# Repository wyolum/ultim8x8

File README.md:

# ultim8x8

ultim8x8 is an APA102 RGB LED based panel consisting of 8x8 matrix. Panels can be chained to produce larger matrices. Besides +5V and GND, each board requires a CLocK and DATa signal. Each board has CLocK and DATa IN and OUT terminals. When cascading boards, the OUT from one board goes to the IN of the next board.

Each LED can require up to 60mA current at 5V for White light at full brightness. This means driving ALL the 64 LEDs at full brightness White color will require 3.8A Amps. You can get away with lower Amps if you drive LEDs at lower brightness or don't light them all up at the same time.

Boards can be cascaded using several methods. Simplest, which requires no soldering, is to screw in the supplied metal posts to the terminals marked +5V, GND, DI__A, CI__A, DO__H and CO__H. The Boards can then be interconnected using the ultim_BUS busbar, or copper tape stuck over a piece of acrylic.

When running at low Amps or driving a single board, the 4 pin 0.1" pitch header can be used.

## kicad

* [ultim8x8_v0](/kicad/ultim_8x8_v0) - first version, Main hardware design files. Schematic, Layout etc. (deprecated)
* [ultim8x8_v1](/kicad/ultim_8x8_v1) - second version, Main hardware design files. Schematic, Layout etc. (deprecated)
* [ultim8x8_v2](/kicad/ultim_8x8_v2) - third version, Main hardware design files. Schematic, Layout etc. (current)

* [ultim_bus_v1](/kicad/ultim_bus_v1) - first version, Hardware design files for a bus bar to inter-connect ultim8x8's (deprecated)
* [ultim_bus_v2](/kicad/ultim_bus_v2) - second version, Hardware design files for a bus bar to inter-connect ultim8x8's (deprecated)
* [ultim_bus_v3](/kicad/ultim_bus_v3) - third version, Hardware design files for a bus bar to inter-connect ultim8x8's (deprecated)
* [ultim_bus_v4](/kicad/ultim_bus_v4) - fourth version, Hardware design files for a bus bar to inter-connect ultim8x8's (deprecated)
* [ultim_bus_v5](/kicad/ultim_bus_v5) - fifth version, Hardware design files for a bus bar to inter-connect ultim8x8's (current)

* [ultim_bus_conn](/kicad/ultim_bus_conn) - connector strips to join multiple ultim__bus_bars

* [featherboard](/kicad/featherboard) - first version, Interface board to connect Adafruit Feather Huzzah board to ultim8x8
* [feather_v2](/kicad/feather_v2) - second version, Interface board to connect Adafruit Feather Huzzah board to ultim8x8
* [feather_v3](/kicad/feather_v3) - third version, Interface board to connect Adafruit Feather Huzzah board to ultim8x8

* [ultim8x8_data](/kicad/ultim8x8_data) - Data sheets, logos etc

## fabricate

* [buckle](/fabricate/buckle) - 3D CAD files for a Belt Buckle.
* [featherboard_case](/fabricate/featherboard_case) - 3D CAD files for a "wireless" ultim8x8 brick

License
-------
[CERN Open Hardware Licence v1.2 ]

[CERN Open Hardware Licence v1.2 ]:http://www.ohwr.org/attachments/2388/cern_ohl_v_1_2.txt

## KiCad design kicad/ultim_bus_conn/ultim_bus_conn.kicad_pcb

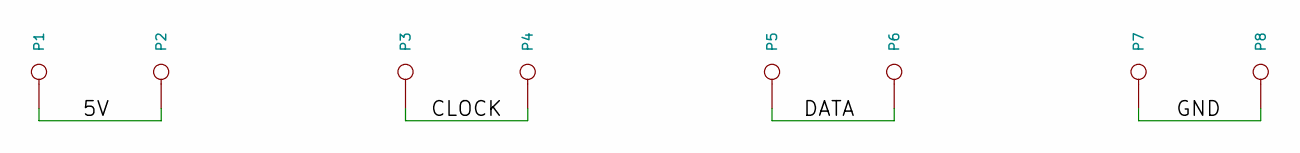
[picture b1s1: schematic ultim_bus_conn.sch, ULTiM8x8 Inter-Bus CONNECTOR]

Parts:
P1, P2, P3, P4, P5, P6, P7, P8: CONN_1; Screw

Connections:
/5V: P1.1, P2.1
/CLOCK: P3.1, P4.1
/DATA: P5.1, P6.1
/GND: P7.1, P8.1

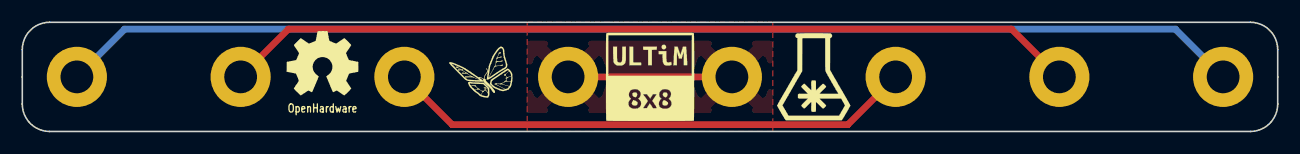
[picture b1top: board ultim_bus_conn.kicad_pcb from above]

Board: 2 copper layers, 116.8 x 10.2 mm, 10 parts (1 on the bottom side), 4 nets.

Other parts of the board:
L101, L101#2: OSHW; OSHW_6mm

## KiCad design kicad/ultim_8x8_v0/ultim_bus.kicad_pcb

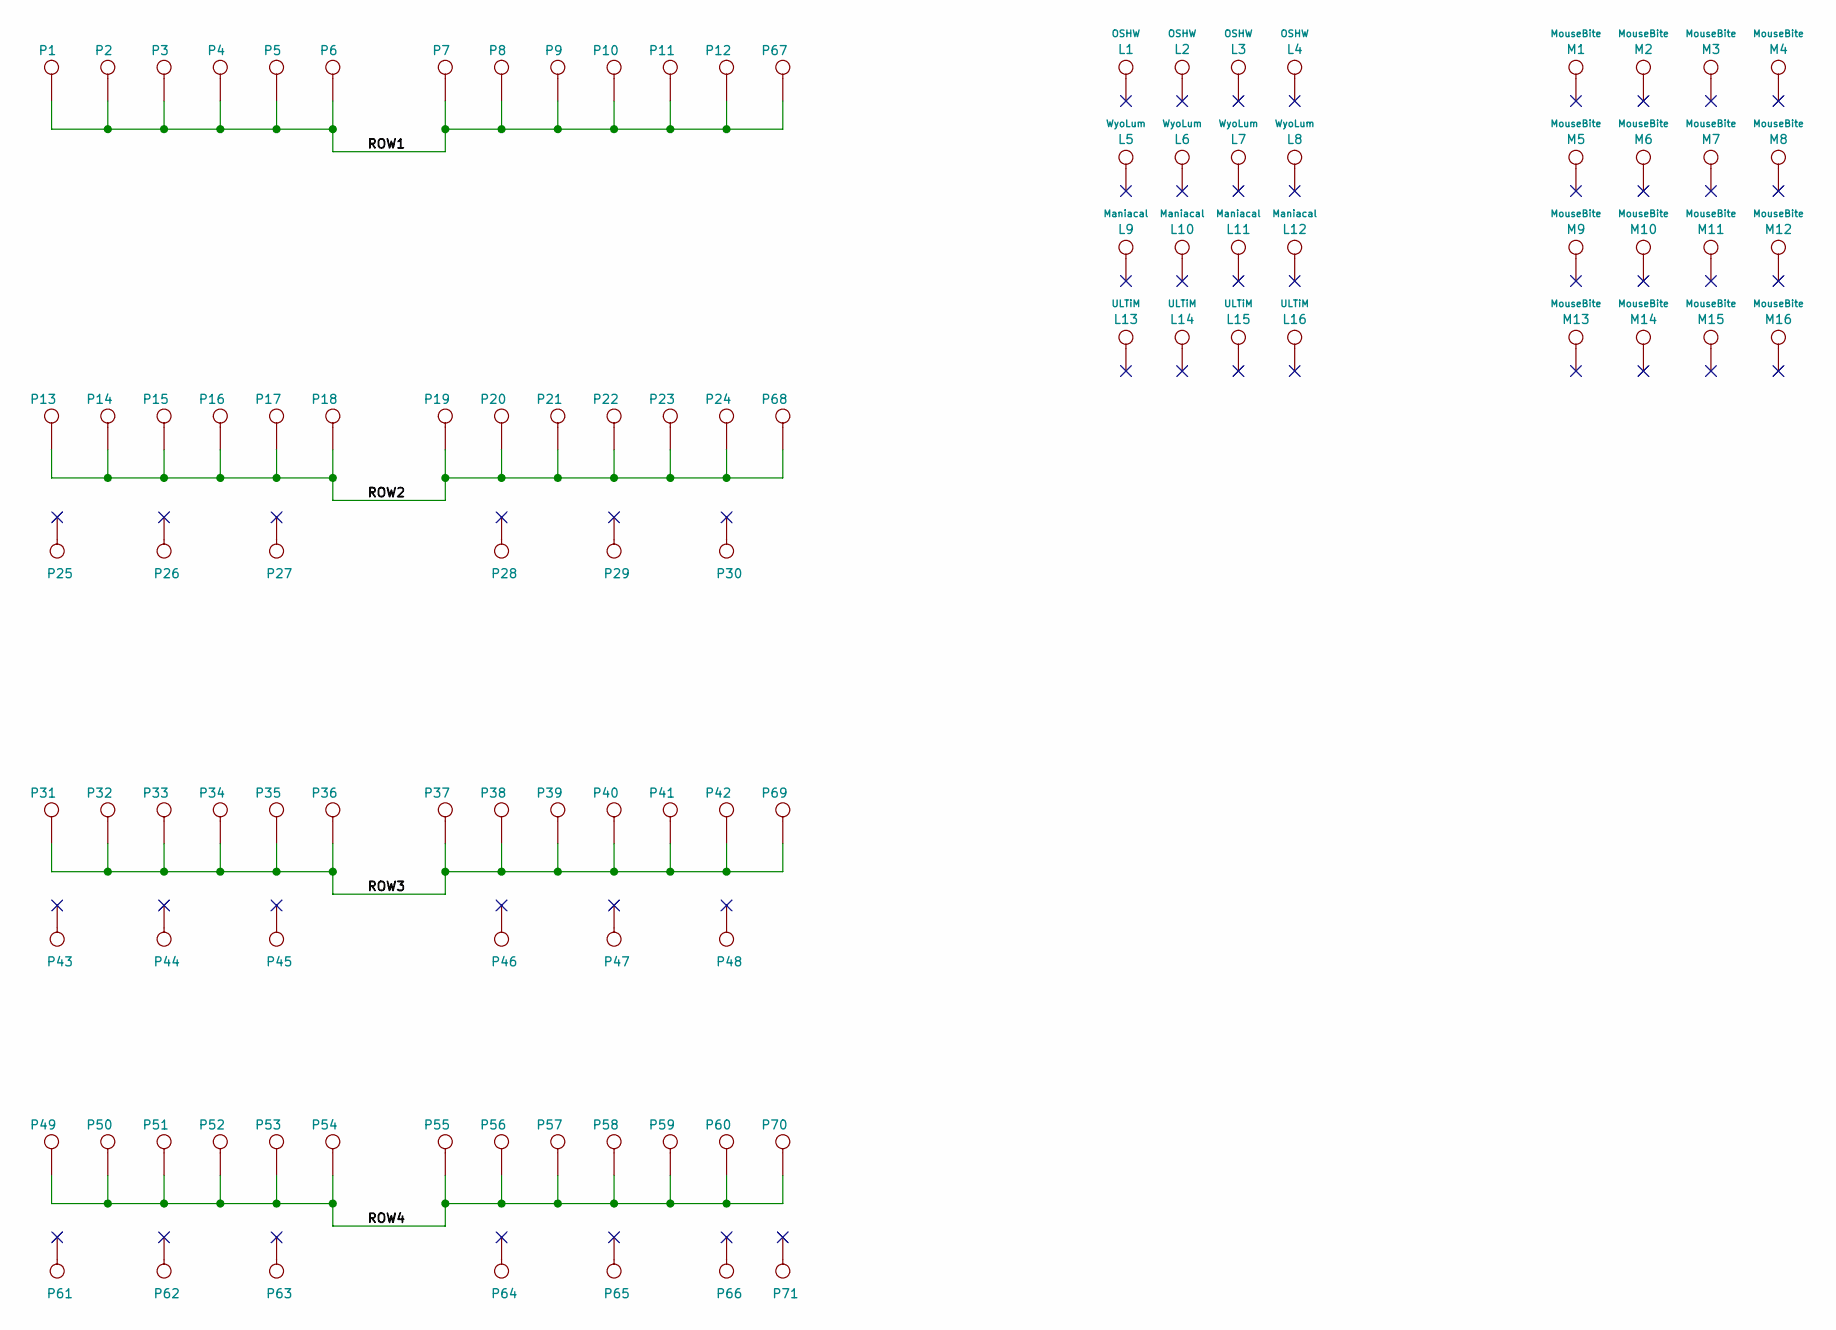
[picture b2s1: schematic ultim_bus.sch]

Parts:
L1, L2, L3, L4: OSHW; OSHW_6mm
L5, L6, L7, L8: WyoLum; logo_wyo_butterfly_small
L9, L10, L11, L12: Maniacal; logo_MLlabs_small
L13, L14, L15, L16: ULTiM; logo_ultim8x8_small
M1, M2, M3, M4, M5, M6, M7, M8, M9, M10, M11, M12, M13, M14, M15, M16: MouseBite; mouse-bite-2.54mm-slot
P1, P2, P3, P4, P5, P6, P7, P8, P9, P10, P11, P12, P13, P14, P15, P16, P17, P18, P19, P20, P21, P22, P23, P24, P25, P26, P27, P28, P29, P30, P31, P32, P33, P34, P35, P36, P37, P38, P39, P40, P41, P42, P43, P44, P45, P46, P47, P48, P49, P50, P51, P52, P53, P54, P55, P56, P57, P58, P59, P60, P61, P62, P63, P64, P65, P66, P67, P68, P69, P70, P71: CONN_1; Screw

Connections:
/ROW1: P1.1, P2.1, P3.1, P4.1, P5.1, P6.1, P7.1, P8.1, P9.1, P10.1, P11.1, P12.1, P67.1
/ROW2: P13.1, P14.1, P15.1, P16.1, P17.1, P18.1, P19.1, P20.1, P21.1, P22.1, P23.1, P24.1, P68.1
/ROW3: P31.1, P32.1, P33.1, P34.1, P35.1, P36.1, P37.1, P38.1, P39.1, P40.1, P41.1, P42.1, P69.1
/ROW4: P49.1, P50.1, P51.1, P52.1, P53.1, P54.1, P55.1, P56.1, P57.1, P58.1, P59.1, P60.1, P70.1

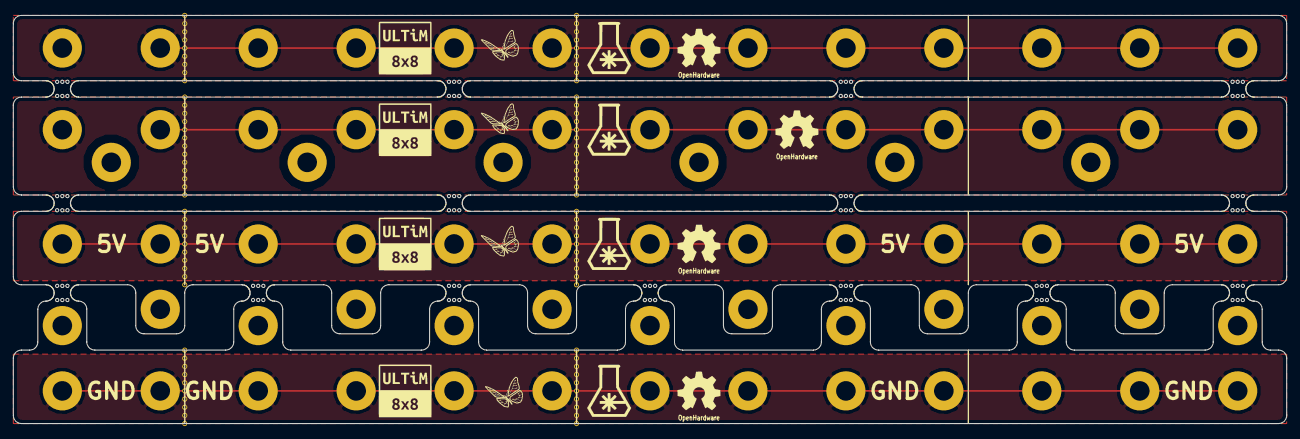
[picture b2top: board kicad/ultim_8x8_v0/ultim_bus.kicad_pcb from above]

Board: 2 copper layers, 198.1 x 63.5 mm, 102 parts (0 on the bottom side), 4 nets.

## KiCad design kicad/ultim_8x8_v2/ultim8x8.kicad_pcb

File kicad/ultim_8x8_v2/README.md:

# ultim_8x8

ultim8x8 is an APA102 RGB LED based panel consisting of 8x8 matrix. Panels can be chained to produce larger matrices. Besides +5V and GND, each board requires a CLocK and DATa signal. Each board has CLocK and DATa IN and OUT terminals. When cascading boards, the OUT from one board goes to the IN of the next board.

Each LED can require up to 60mA current at 5V for White light at full brightness. This means driving ALL the 64 LEDs at full brightness White color will require 3.8A Amps. You can get away with lower Amps if you drive LEDs at lower brightness or don't light them all up at the same time.

Boards can be cascaded using several methods. Simplest, which requires no soldering, is to screw in the supplied metal posts to the terminals marked +5V, GND, D_IN, C_IN, D_OUT and C_OUT. The Boards can then be interconnected using the ultim_BUS busbar, or copper tape stuck over a piece of acrylic.

When running at low Amps or driving a single board, the 4 pin 0.1" pitch headers can be used. There are two pairs of headers marked In1/Out1 and In2/Out2.

License
-------
[CERN Open Hardware Licence v1.2 ]

[CERN Open Hardware Licence v1.2 ]:http://www.ohwr.org/attachments/2388/cern_ohl_v_1_2.txt

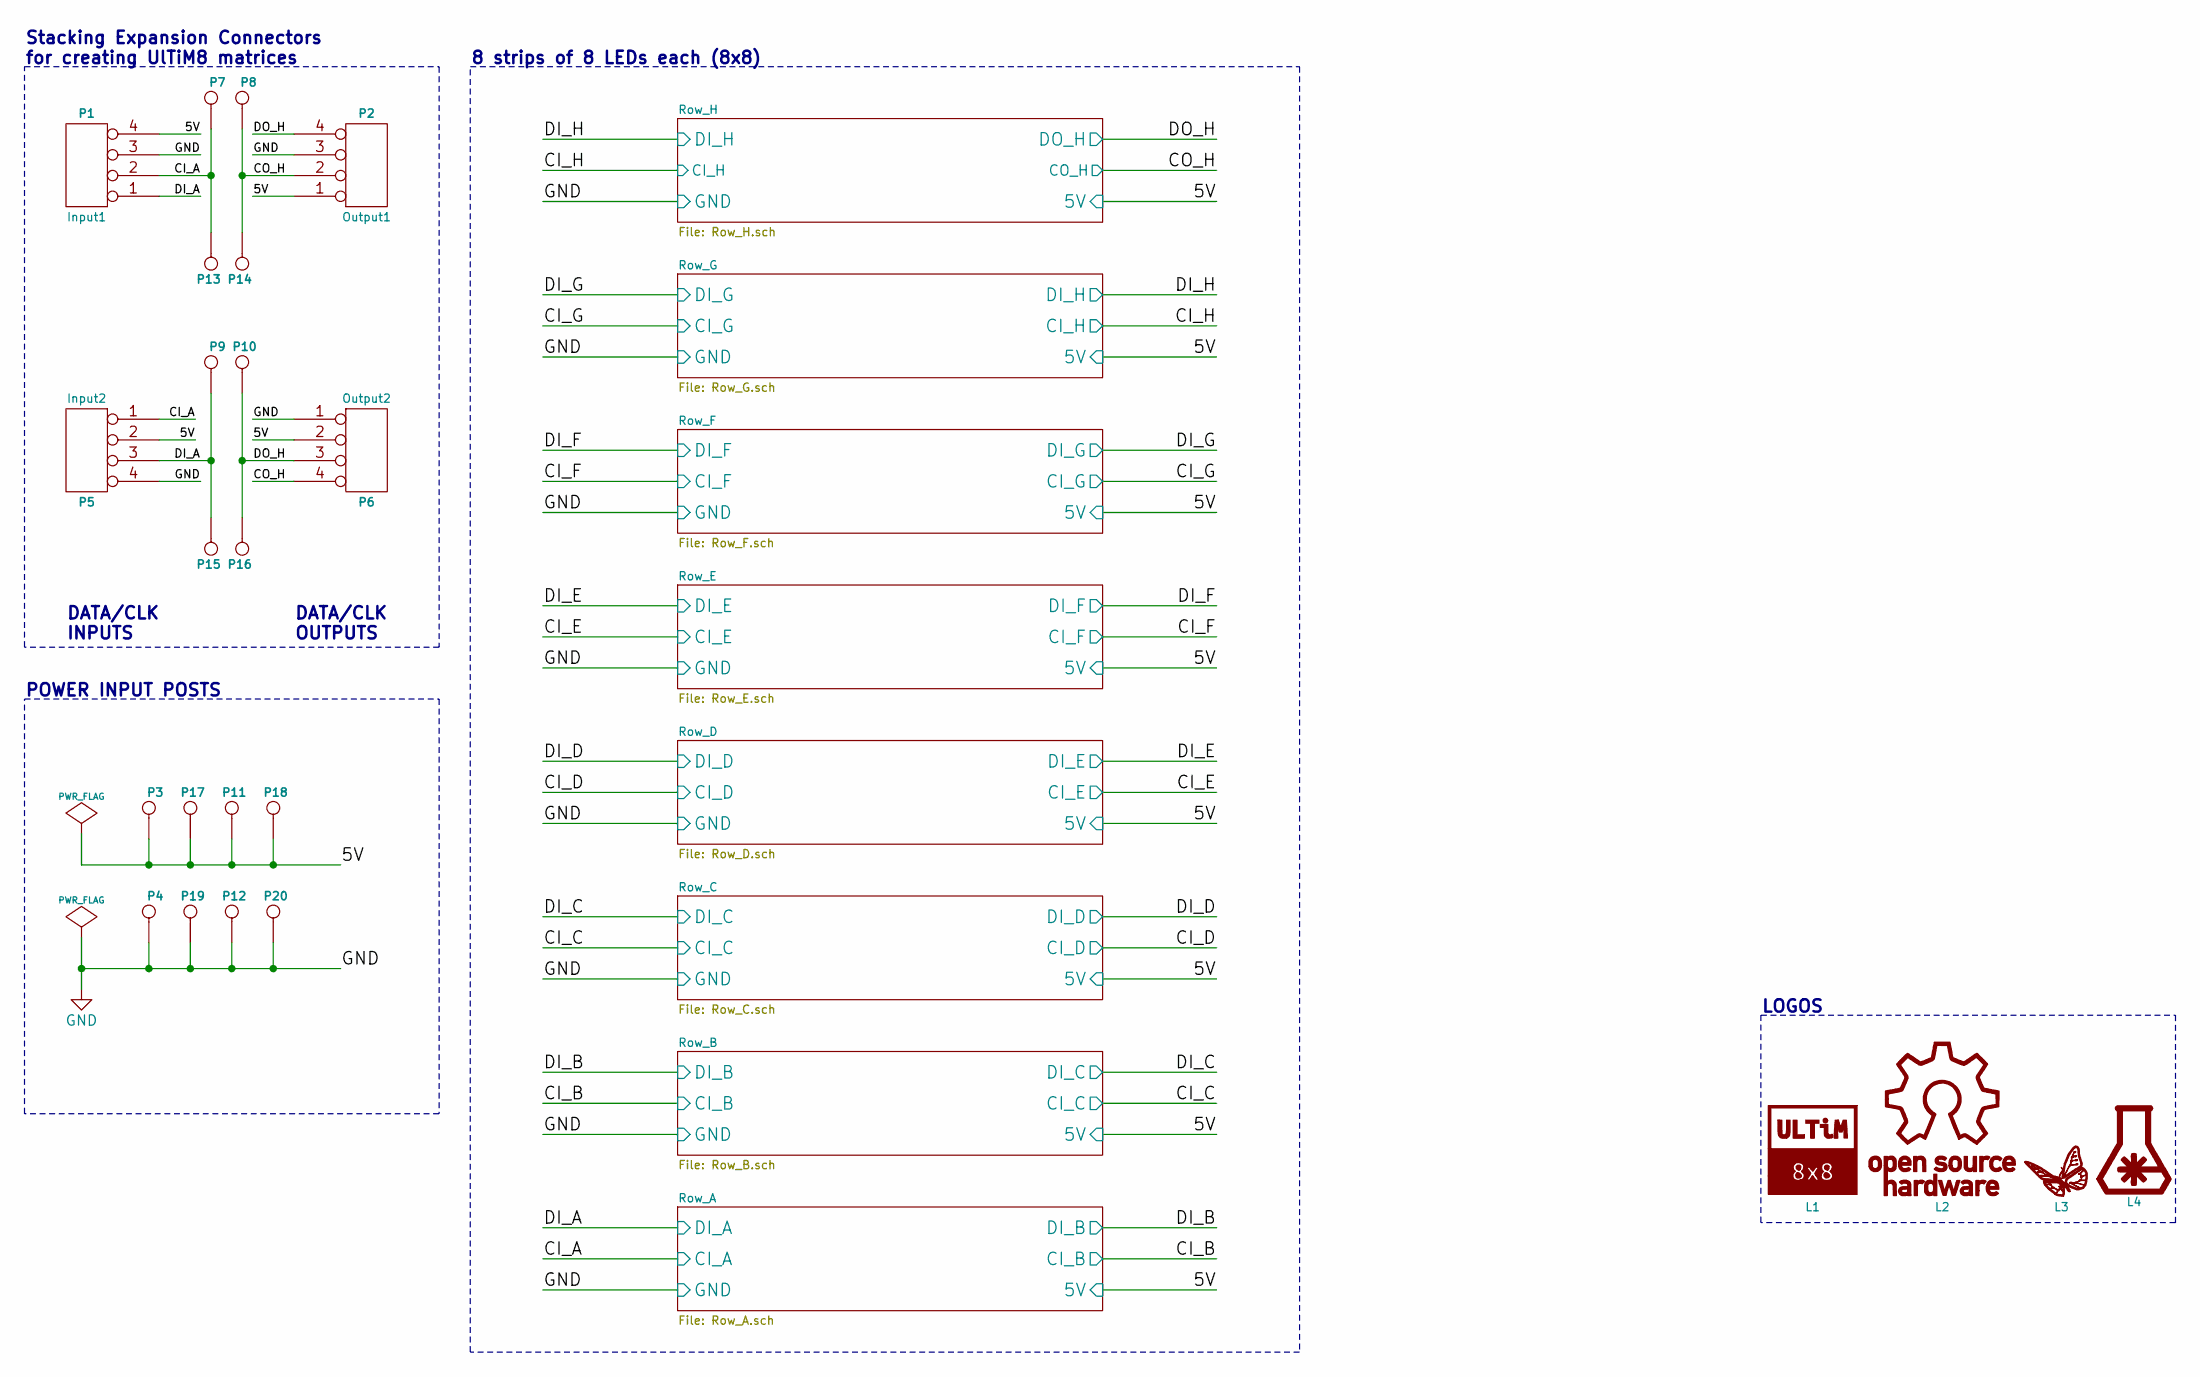
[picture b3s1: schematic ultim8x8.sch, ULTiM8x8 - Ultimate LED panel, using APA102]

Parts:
L1: ULTiM8x8; logo_ultim8x8_7mm
L2: OSHW; OSHW_6mm
L3: Wyolum; logo_wyo_butterfly_5mm
L4: Maniacal Labs; logo_MLlabs_5mm
P1: Input1; header_2x2pos_th_male
P2: Output1; header_2x2pos_th_male
P3, P11, P17, P18: 5V; Screw
P4, P12, P19, P20: GND; Screw
P5: Input2; header_2x2pos_th_male
P6: Output2; header_2x2pos_th_male
P7, P13: CI_A; Screw
P8, P14: CO_H; Screw
P9, P15: DI_A; Screw
P10, P16: DO_H; Screw

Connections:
/5V: P1.4, P2.1, P3.1, P5.2, P6.2, P11.1, P17.1, P18.1; also elsewhere on the board
/CI_A: P1.2, P5.1, P7.1, P13.1; also elsewhere on the board
/CO_H: P2.2, P6.4, P8.1, P14.1; also elsewhere on the board
/DI_A: P1.1, P5.3, P9.1, P15.1; also elsewhere on the board
/DO_H: P2.4, P6.3, P10.1, P16.1; also elsewhere on the board
GND: P1.3, P2.3, P4.1, P5.4, P6.1, P12.1, P19.1, P20.1; also elsewhere on the board

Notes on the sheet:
Stacking Expansion Connectors for creating UlTiM8 matrices
LOGOS
POWER INPUT POSTS
DATA/CLK OUTPUTS
DATA/CLK INPUTS
8 strips of 8 LEDs each (8x8)

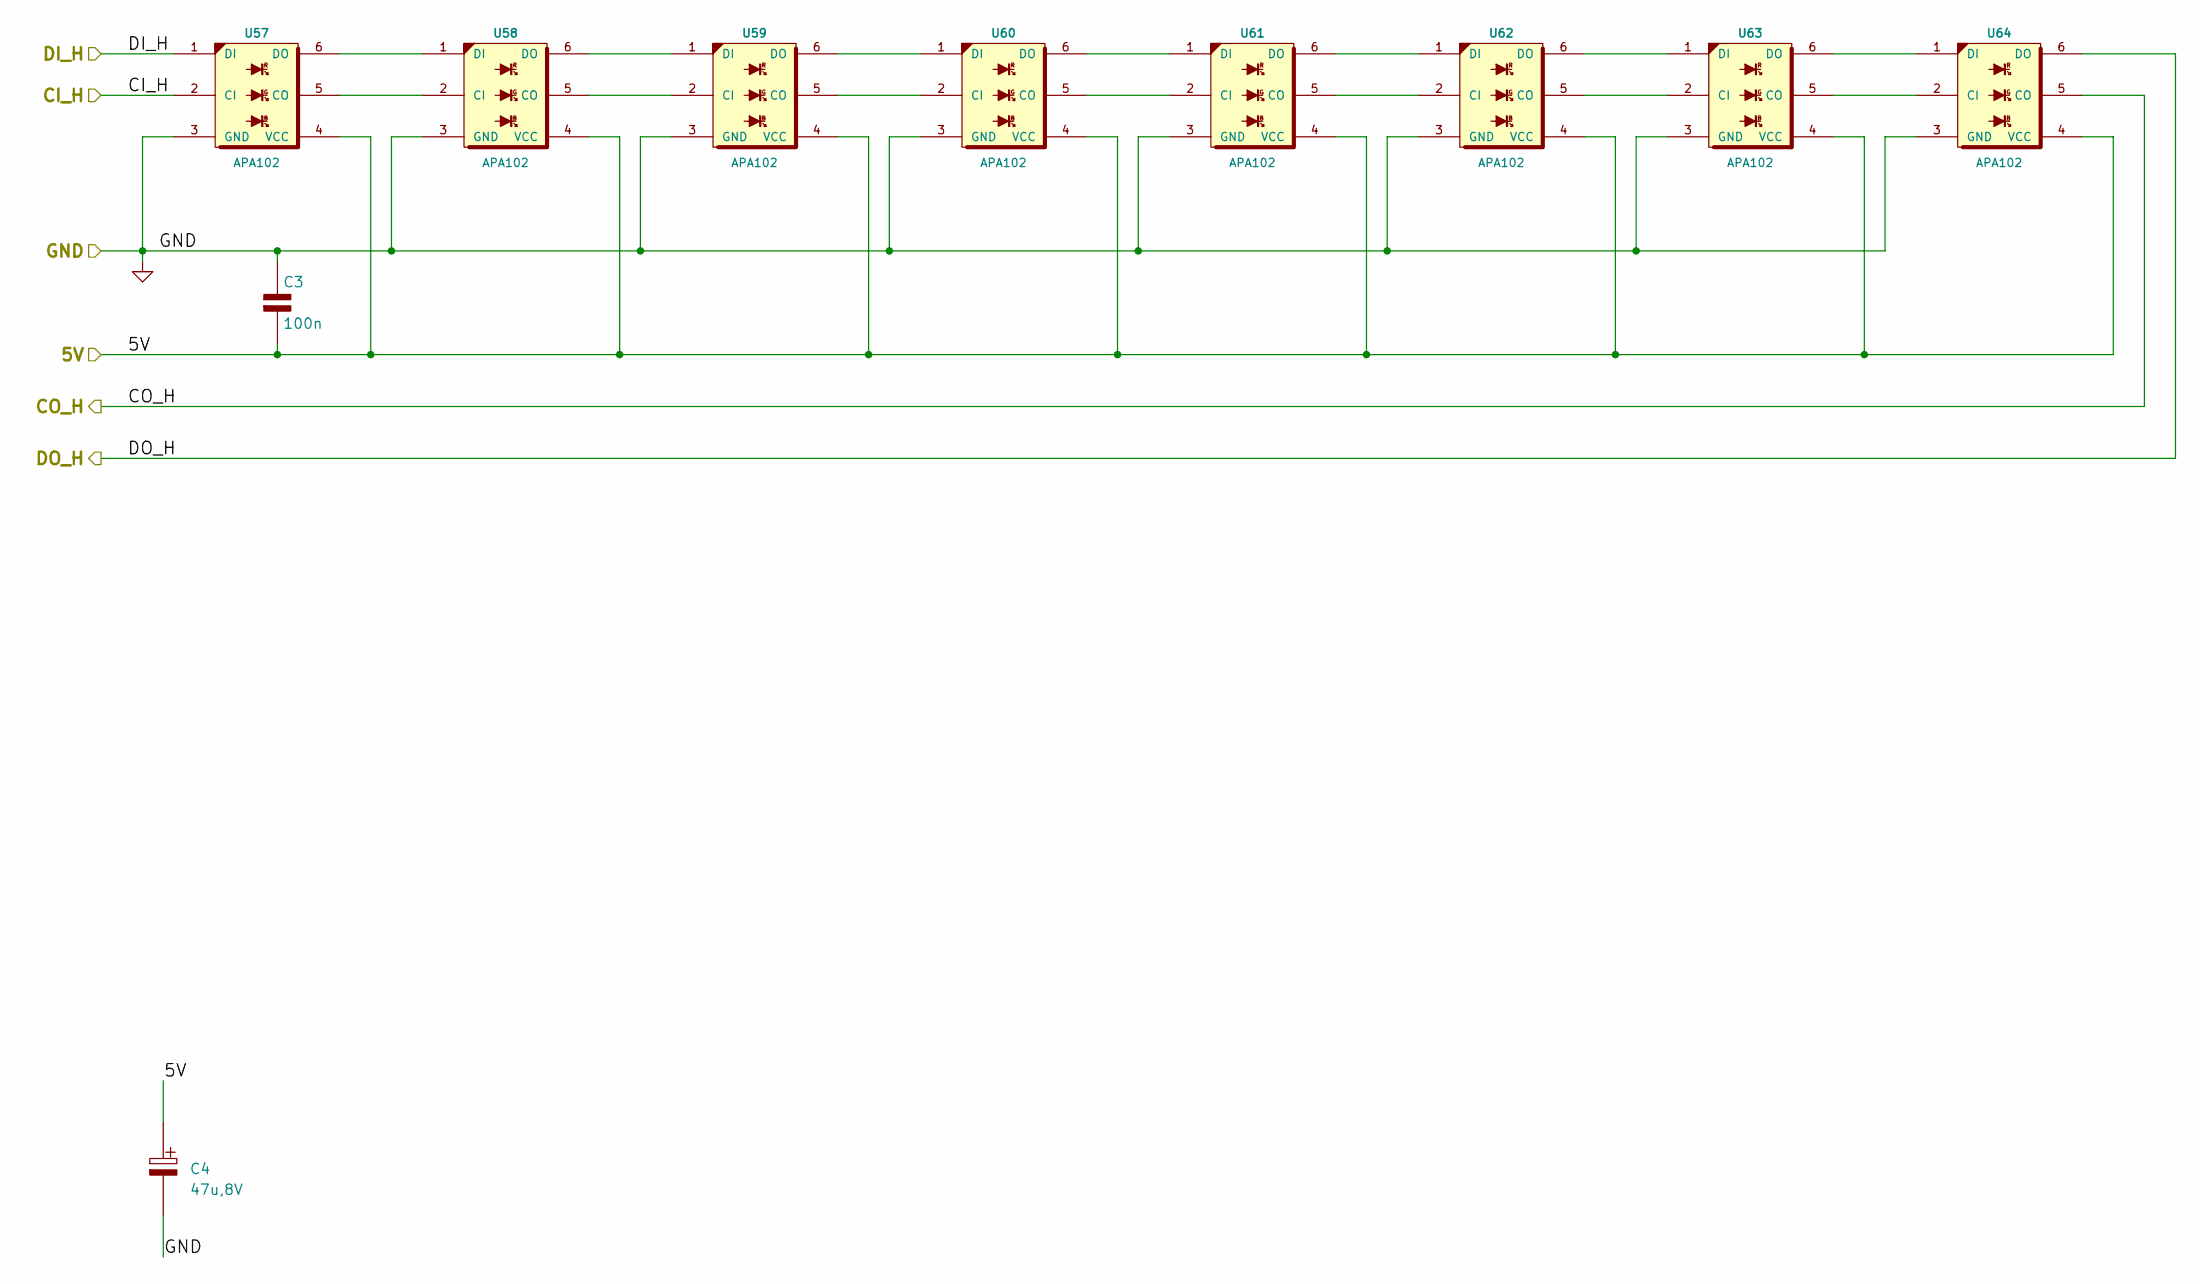
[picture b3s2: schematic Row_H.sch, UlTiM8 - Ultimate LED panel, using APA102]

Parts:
C3: 100n; c_0805
C4: 47u,8V; c_2917
U57, U58, U59, U60, U61, U62, U63, U64: APA102

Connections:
/5V: C3.2, C4.1 (+), U57.4 (VCC), U58.4 (VCC), U59.4 (VCC), U60.4 (VCC), U61.4 (VCC), U62.4 (VCC), U63.4 (VCC), U64.4 (VCC); also elsewhere on the board
/CI_H: U57.2 (CI); also elsewhere on the board
/CO_H: U64.5 (CO); also elsewhere on the board
/DI_H: U57.1 (DI); also elsewhere on the board
/DO_H: U64.6 (DO); also elsewhere on the board
GND: C3.1, C4.2 (-), U57.3 (GND), U58.3 (GND), U59.3 (GND), U60.3 (GND), U61.3 (GND), U62.3 (GND), U63.3 (GND), U64.3 (GND); also elsewhere on the board
unnamed: U57.5 (CO), U58.2 (CI)
unnamed: U57.6 (DO), U58.1 (DI)
unnamed: U58.5 (CO), U59.2 (CI)
unnamed: U58.6 (DO), U59.1 (DI)
unnamed: U59.5 (CO), U60.2 (CI)
unnamed: U59.6 (DO), U60.1 (DI)
unnamed: U60.5 (CO), U61.2 (CI)
unnamed: U60.6 (DO), U61.1 (DI)
unnamed: U61.5 (CO), U62.2 (CI)
unnamed: U61.6 (DO), U62.1 (DI)
unnamed: U62.5 (CO), U63.2 (CI)
unnamed: U62.6 (DO), U63.1 (DI)
unnamed: U63.5 (CO), U64.2 (CI)
unnamed: U63.6 (DO), U64.1 (DI)

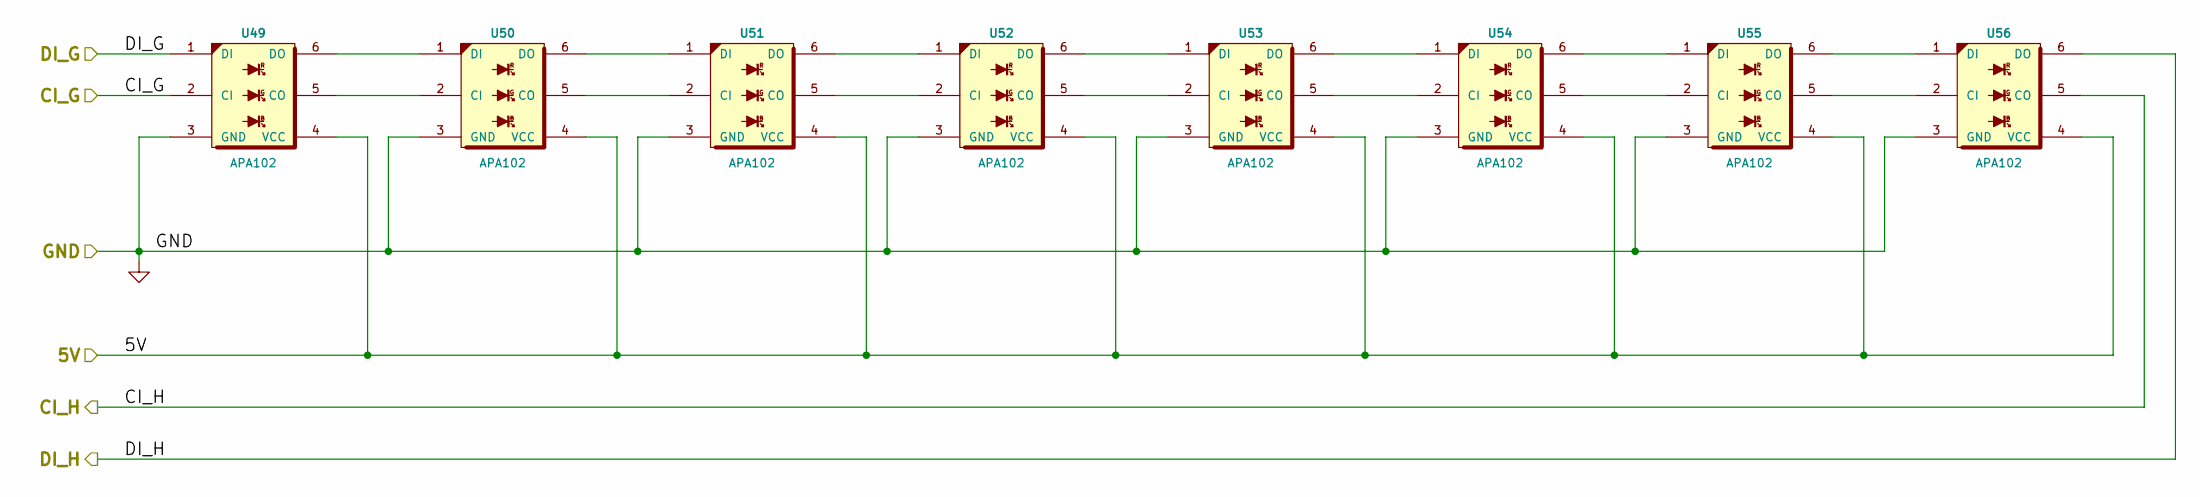
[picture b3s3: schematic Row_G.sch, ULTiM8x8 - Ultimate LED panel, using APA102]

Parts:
U49, U50, U51, U52, U53, U54, U55, U56: APA102

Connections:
/5V: U49.4 (VCC), U50.4 (VCC), U51.4 (VCC), U52.4 (VCC), U53.4 (VCC), U54.4 (VCC), U55.4 (VCC), U56.4 (VCC); also elsewhere on the board
/CI_G: U49.2 (CI); also elsewhere on the board
/CI_H: U56.5 (CO); also elsewhere on the board
/DI_G: U49.1 (DI); also elsewhere on the board
/DI_H: U56.6 (DO); also elsewhere on the board
GND: U49.3 (GND), U50.3 (GND), U51.3 (GND), U52.3 (GND), U53.3 (GND), U54.3 (GND), U55.3 (GND), U56.3 (GND); also elsewhere on the board
unnamed: U49.5 (CO), U50.2 (CI)
unnamed: U49.6 (DO), U50.1 (DI)
unnamed: U50.5 (CO), U51.2 (CI)
unnamed: U50.6 (DO), U51.1 (DI)
unnamed: U51.5 (CO), U52.2 (CI)
unnamed: U51.6 (DO), U52.1 (DI)
unnamed: U52.5 (CO), U53.2 (CI)
unnamed: U52.6 (DO), U53.1 (DI)
unnamed: U53.5 (CO), U54.2 (CI)
unnamed: U53.6 (DO), U54.1 (DI)
unnamed: U54.5 (CO), U55.2 (CI)
unnamed: U54.6 (DO), U55.1 (DI)
unnamed: U55.5 (CO), U56.2 (CI)
unnamed: U55.6 (DO), U56.1 (DI)

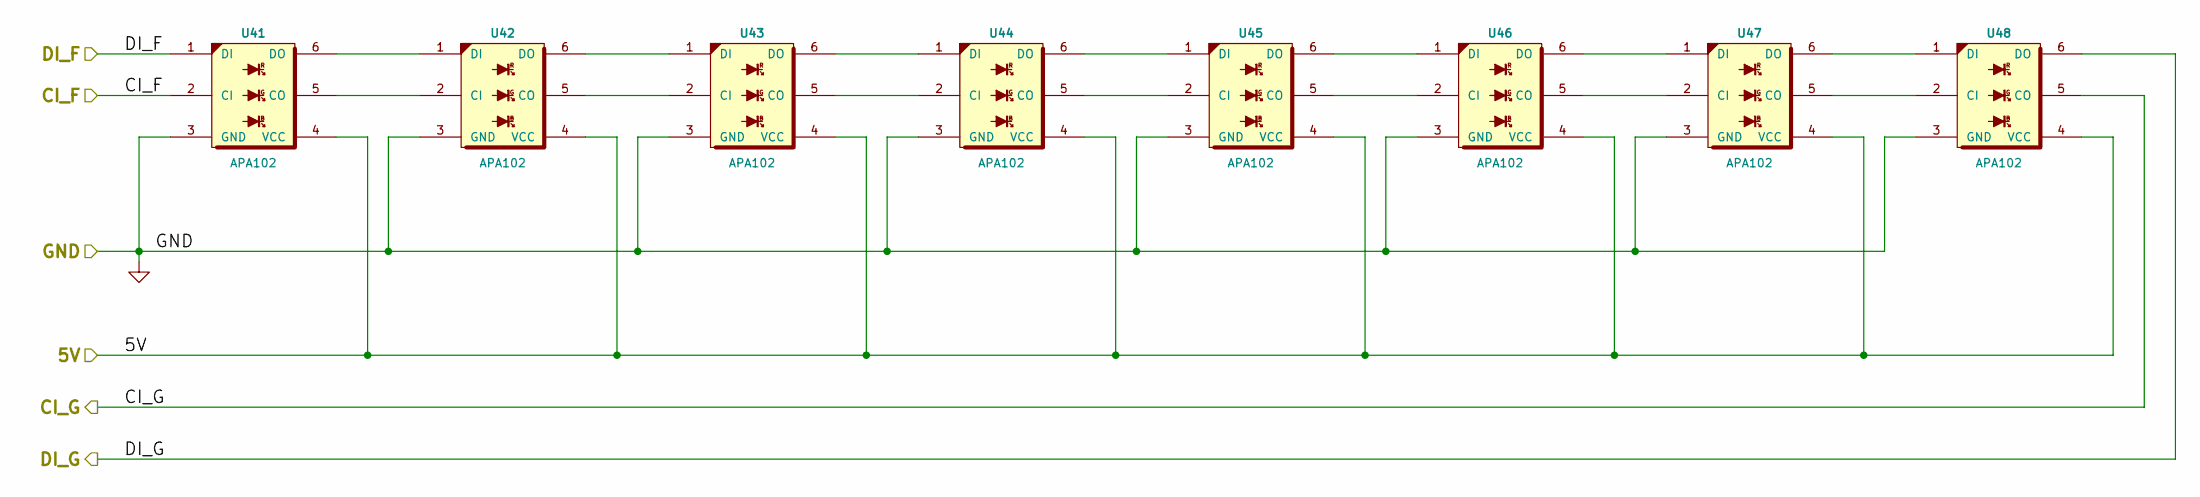
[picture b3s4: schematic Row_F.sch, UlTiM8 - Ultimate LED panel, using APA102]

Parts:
U41, U42, U43, U44, U45, U46, U47, U48: APA102

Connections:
/5V: U41.4 (VCC), U42.4 (VCC), U43.4 (VCC), U44.4 (VCC), U45.4 (VCC), U46.4 (VCC), U47.4 (VCC), U48.4 (VCC); also elsewhere on the board
/CI_F: U41.2 (CI); also elsewhere on the board
/CI_G: U48.5 (CO); also elsewhere on the board
/DI_F: U41.1 (DI); also elsewhere on the board
/DI_G: U48.6 (DO); also elsewhere on the board
GND: U41.3 (GND), U42.3 (GND), U43.3 (GND), U44.3 (GND), U45.3 (GND), U46.3 (GND), U47.3 (GND), U48.3 (GND); also elsewhere on the board
unnamed: U41.5 (CO), U42.2 (CI)
unnamed: U41.6 (DO), U42.1 (DI)
unnamed: U42.5 (CO), U43.2 (CI)
unnamed: U42.6 (DO), U43.1 (DI)
unnamed: U43.5 (CO), U44.2 (CI)
unnamed: U43.6 (DO), U44.1 (DI)
unnamed: U44.5 (CO), U45.2 (CI)
unnamed: U44.6 (DO), U45.1 (DI)
unnamed: U45.5 (CO), U46.2 (CI)
unnamed: U45.6 (DO), U46.1 (DI)
unnamed: U46.5 (CO), U47.2 (CI)
unnamed: U46.6 (DO), U47.1 (DI)
unnamed: U47.5 (CO), U48.2 (CI)
unnamed: U47.6 (DO), U48.1 (DI)

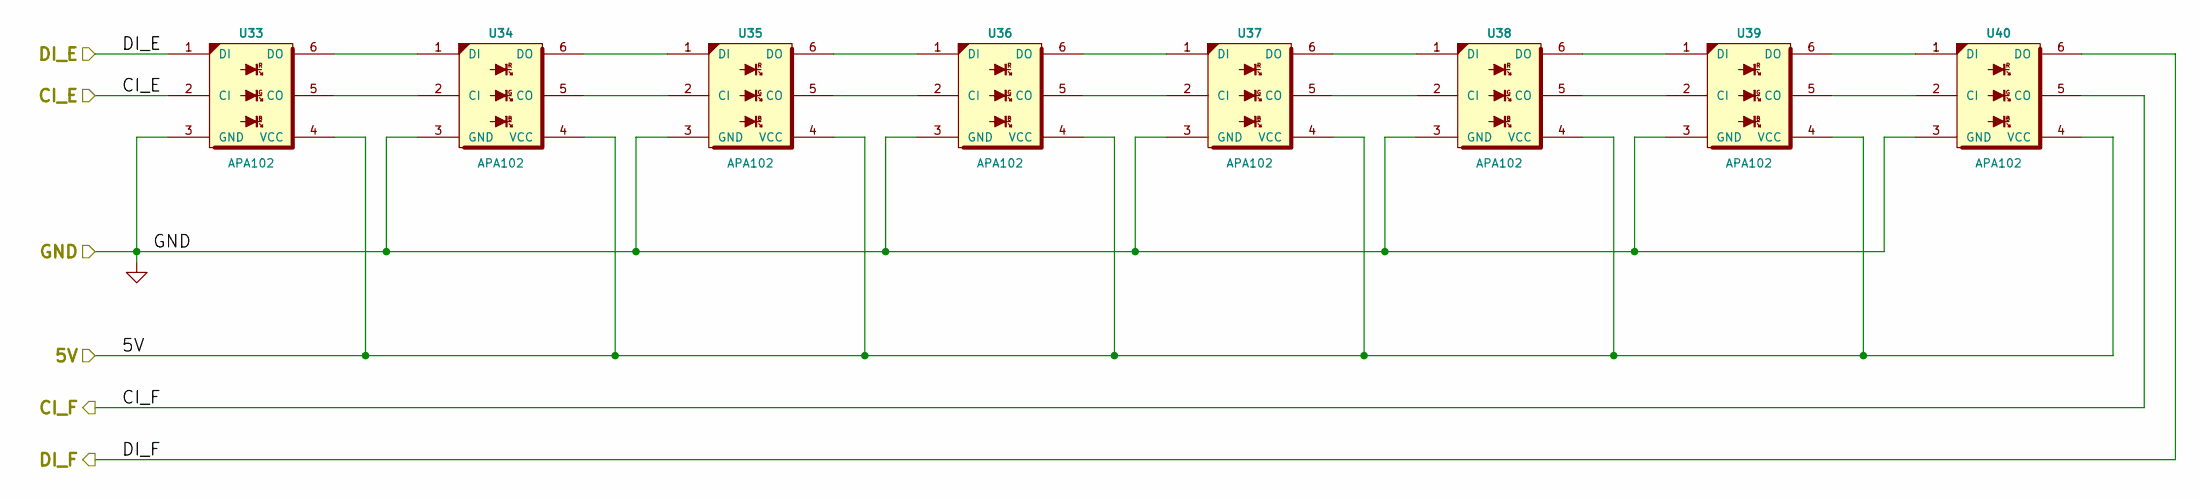
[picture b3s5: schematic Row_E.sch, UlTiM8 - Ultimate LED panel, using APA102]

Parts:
U33, U34, U35, U36, U37, U38, U39, U40: APA102

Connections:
/5V: U33.4 (VCC), U34.4 (VCC), U35.4 (VCC), U36.4 (VCC), U37.4 (VCC), U38.4 (VCC), U39.4 (VCC), U40.4 (VCC); also elsewhere on the board
/CI_E: U33.2 (CI); also elsewhere on the board
/CI_F: U40.5 (CO); also elsewhere on the board
/DI_E: U33.1 (DI); also elsewhere on the board
/DI_F: U40.6 (DO); also elsewhere on the board
GND: U33.3 (GND), U34.3 (GND), U35.3 (GND), U36.3 (GND), U37.3 (GND), U38.3 (GND), U39.3 (GND), U40.3 (GND); also elsewhere on the board
unnamed: U33.5 (CO), U34.2 (CI)
unnamed: U33.6 (DO), U34.1 (DI)
unnamed: U34.5 (CO), U35.2 (CI)
unnamed: U34.6 (DO), U35.1 (DI)
unnamed: U35.5 (CO), U36.2 (CI)
unnamed: U35.6 (DO), U36.1 (DI)
unnamed: U36.5 (CO), U37.2 (CI)
unnamed: U36.6 (DO), U37.1 (DI)
unnamed: U37.5 (CO), U38.2 (CI)
unnamed: U37.6 (DO), U38.1 (DI)
unnamed: U38.5 (CO), U39.2 (CI)
unnamed: U38.6 (DO), U39.1 (DI)
unnamed: U39.5 (CO), U40.2 (CI)
unnamed: U39.6 (DO), U40.1 (DI)

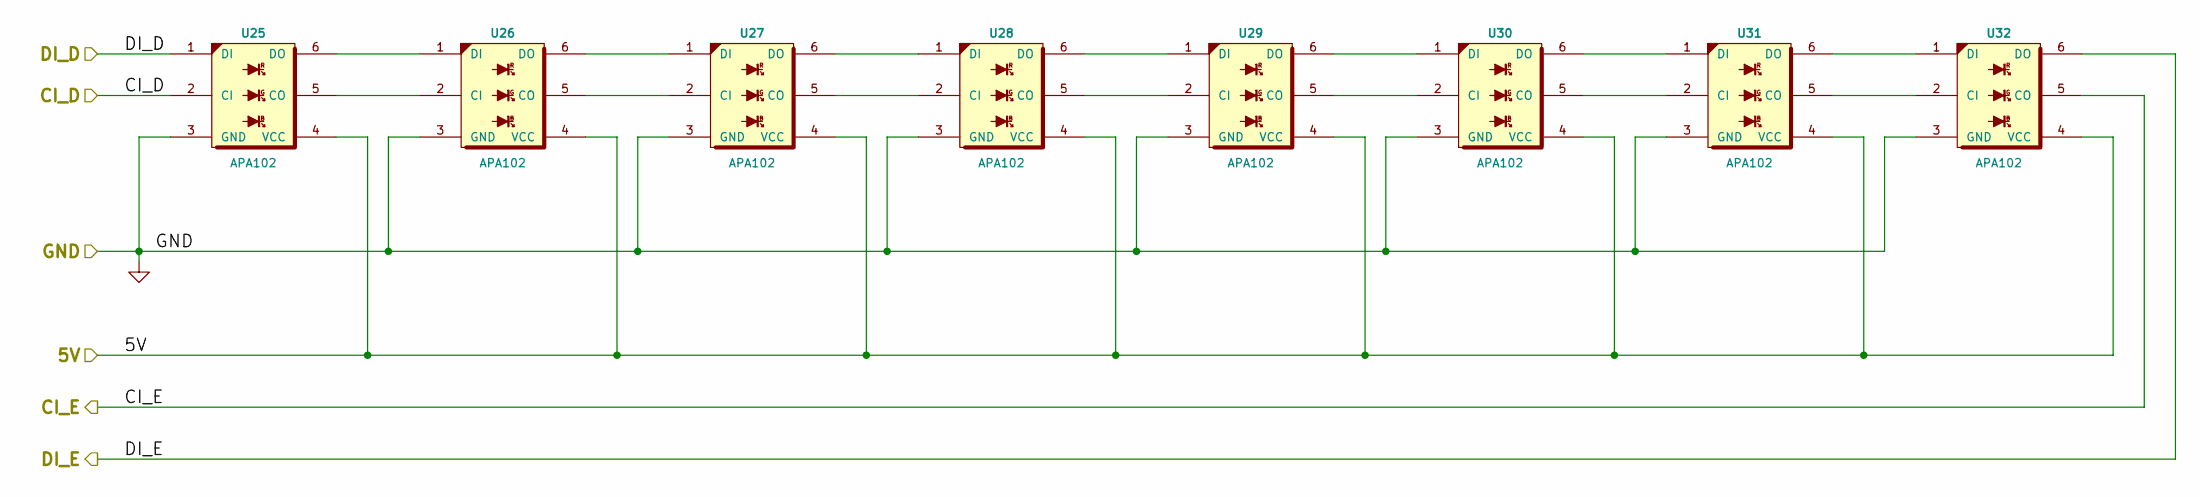
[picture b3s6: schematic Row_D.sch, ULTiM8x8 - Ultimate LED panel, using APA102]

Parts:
U25, U26, U27, U28, U29, U30, U31, U32: APA102

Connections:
/5V: U25.4 (VCC), U26.4 (VCC), U27.4 (VCC), U28.4 (VCC), U29.4 (VCC), U30.4 (VCC), U31.4 (VCC), U32.4 (VCC); also elsewhere on the board
/CI_D: U25.2 (CI); also elsewhere on the board
/CI_E: U32.5 (CO); also elsewhere on the board
/DI_D: U25.1 (DI); also elsewhere on the board
/DI_E: U32.6 (DO); also elsewhere on the board
GND: U25.3 (GND), U26.3 (GND), U27.3 (GND), U28.3 (GND), U29.3 (GND), U30.3 (GND), U31.3 (GND), U32.3 (GND); also elsewhere on the board
unnamed: U25.5 (CO), U26.2 (CI)
unnamed: U25.6 (DO), U26.1 (DI)
unnamed: U26.5 (CO), U27.2 (CI)
unnamed: U26.6 (DO), U27.1 (DI)
unnamed: U27.5 (CO), U28.2 (CI)
unnamed: U27.6 (DO), U28.1 (DI)
unnamed: U28.5 (CO), U29.2 (CI)
unnamed: U28.6 (DO), U29.1 (DI)
unnamed: U29.5 (CO), U30.2 (CI)
unnamed: U29.6 (DO), U30.1 (DI)
unnamed: U30.5 (CO), U31.2 (CI)
unnamed: U30.6 (DO), U31.1 (DI)
unnamed: U31.5 (CO), U32.2 (CI)
unnamed: U31.6 (DO), U32.1 (DI)

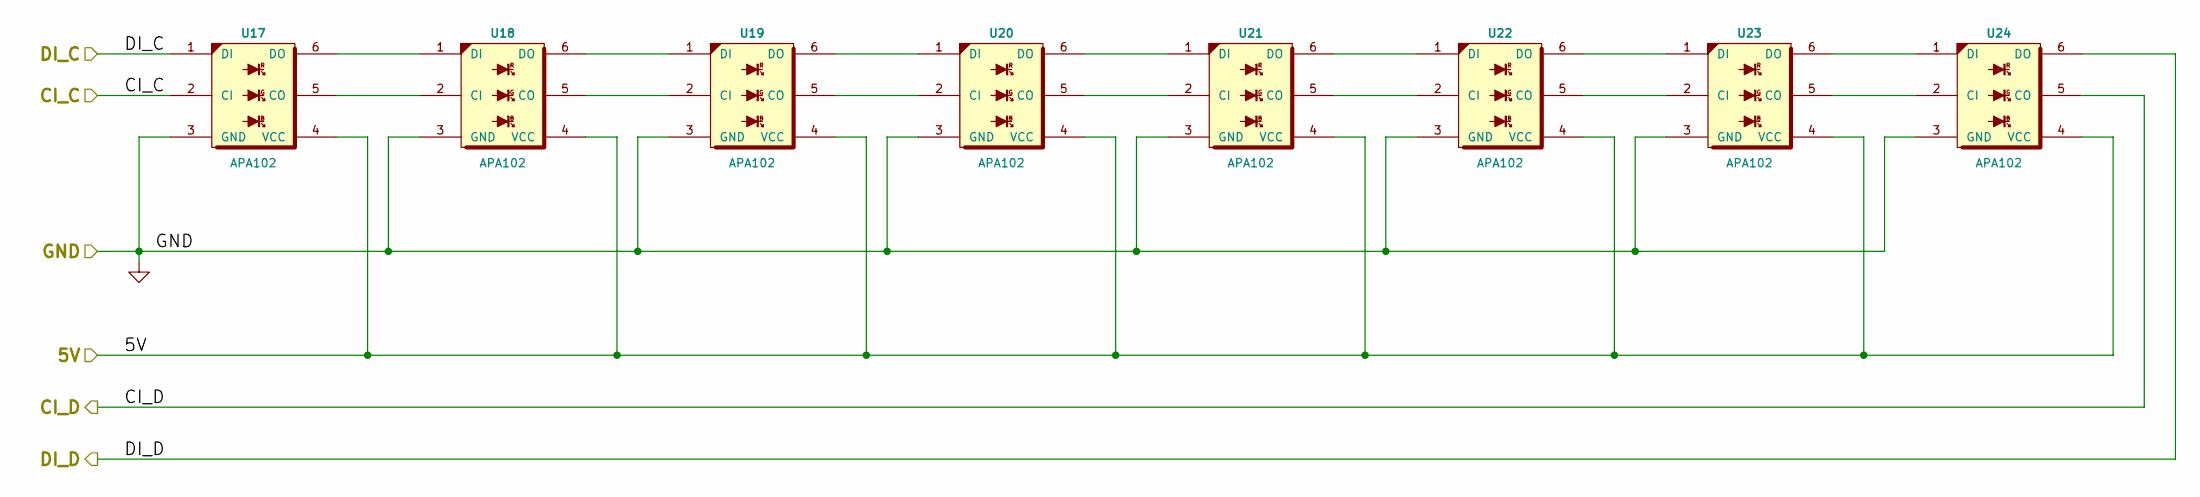
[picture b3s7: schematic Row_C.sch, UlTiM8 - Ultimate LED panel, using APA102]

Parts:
U17, U18, U19, U20, U21, U22, U23, U24: APA102

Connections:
/5V: U17.4 (VCC), U18.4 (VCC), U19.4 (VCC), U20.4 (VCC), U21.4 (VCC), U22.4 (VCC), U23.4 (VCC), U24.4 (VCC); also elsewhere on the board
/CI_C: U17.2 (CI); also elsewhere on the board
/CI_D: U24.5 (CO); also elsewhere on the board
/DI_C: U17.1 (DI); also elsewhere on the board
/DI_D: U24.6 (DO); also elsewhere on the board
GND: U17.3 (GND), U18.3 (GND), U19.3 (GND), U20.3 (GND), U21.3 (GND), U22.3 (GND), U23.3 (GND), U24.3 (GND); also elsewhere on the board
unnamed: U17.5 (CO), U18.2 (CI)
unnamed: U17.6 (DO), U18.1 (DI)
unnamed: U18.5 (CO), U19.2 (CI)
unnamed: U18.6 (DO), U19.1 (DI)
unnamed: U19.5 (CO), U20.2 (CI)
unnamed: U19.6 (DO), U20.1 (DI)
unnamed: U20.5 (CO), U21.2 (CI)
unnamed: U20.6 (DO), U21.1 (DI)
unnamed: U21.5 (CO), U22.2 (CI)
unnamed: U21.6 (DO), U22.1 (DI)
unnamed: U22.5 (CO), U23.2 (CI)
unnamed: U22.6 (DO), U23.1 (DI)
unnamed: U23.5 (CO), U24.2 (CI)
unnamed: U23.6 (DO), U24.1 (DI)
